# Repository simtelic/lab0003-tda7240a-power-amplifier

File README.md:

# TDA7240A Power Amplifier Module

This repository contains the design files and documentation for a compact, high-efficiency TDA7240A-based power amplifier module. Designed for DIY audio enthusiasts, this module delivers up to 20W of audio output power from a 15V DC supply.

**Key Features:**

* **TDA7240A Amplifier IC:** Robust audio amplification with up to 20W output.
* **Aluminum PCB Design:** Excellent thermal conductivity for efficient heat dissipation and easy heatsink mounting.
* **Compact Footprint:** 55.5mm × 35.75mm, ideal for space-constrained projects.

This repository provides:

* Schematics and PCB layout files.
* A Bill of Materials.

This is an open hardware project, and all design files are available in this repository. You can also order an assembled kit from Simtelic.

[PCBWay](https://www.pcbway.com/) sponsors this project, and you can directly order the PCB from them as well.

The datasheet and user manual for this project are available at [simtelic.com](https://simtelic.com/).

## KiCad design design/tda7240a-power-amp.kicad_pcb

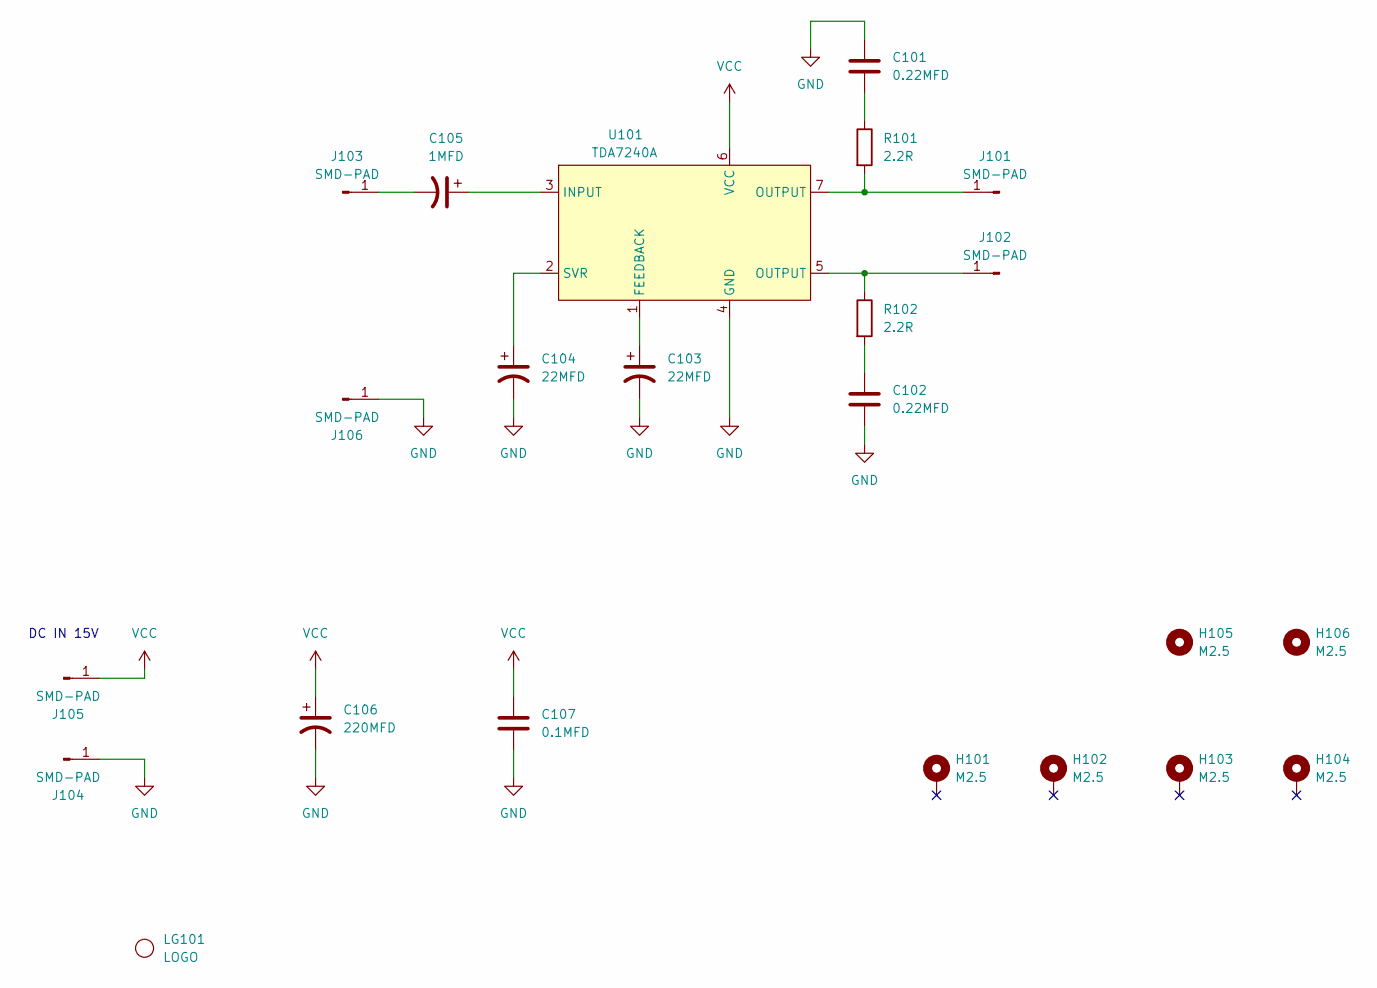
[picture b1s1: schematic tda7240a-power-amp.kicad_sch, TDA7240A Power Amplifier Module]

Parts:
C101, C102: 0.22MFD; C_0805_2012Metric_Pad1.18x1.45mm_HandSolder
C103, C104: 22MFD; CP_Elec_5x5.4
C105: 1MFD; CP_Elec_4x5.4
C106: 220MFD; CP_Elec_8x10.5
C107: 0.1MFD; C_0805_2012Metric_Pad1.18x1.45mm_HandSolder
H101, H102, H103, H104, H105, H106: M2.5; MountingHole_2.5mm
J101, J102, J103, J104, J105, J106: SMD-PAD; TestPoint_Pad_3.0x3.0mm
LG101: LOGO; simtelic-name-5
R101, R102: 2.2R; R_2512_6332Metric_Pad1.40x3.35mm_HandSolder
U101: TDA7240A; ST-Heptawatt-Inline

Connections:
GND: C101.1, C102.2, C103.2, C104.2, C106.2, C107.2, J104.1, J106.1, U101.4 (GND)
unnamed: C101.2, R101.1
unnamed: C102.1, R102.2
unnamed: J101.1, R101.2, U101.7 (OUTPUT)
unnamed: J102.1, R102.1, U101.5 (OUTPUT)
unnamed: C105.2, J103.1
unnamed: C103.1, U101.1 (FEEDBACK)
unnamed: C105.1, U101.3 (INPUT)
unnamed: C104.1, U101.2 (SVR)
VCC: C106.1, C107.1, J105.1, U101.6 (VCC)

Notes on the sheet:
DC IN 15V

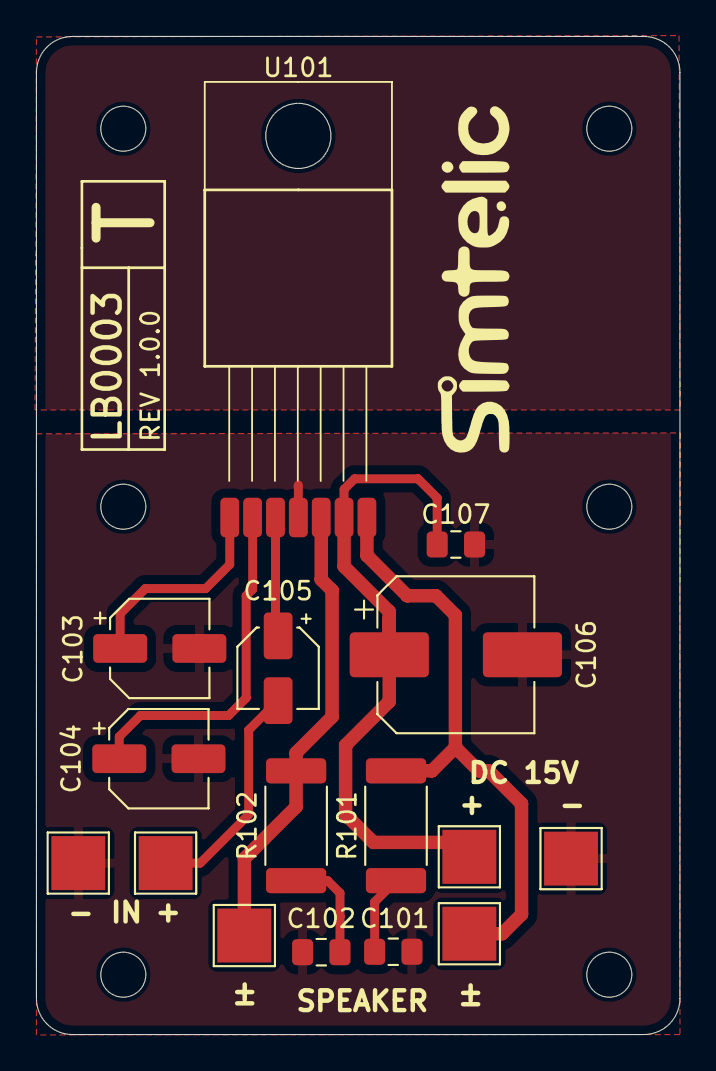
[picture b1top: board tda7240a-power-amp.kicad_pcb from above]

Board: 2 copper layers, 35.8 x 55.5 mm, 23 parts (0 on the bottom side), 10 nets.

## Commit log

2025-03-13 Add initial version of project files.
2025-03-13 Add license file.
